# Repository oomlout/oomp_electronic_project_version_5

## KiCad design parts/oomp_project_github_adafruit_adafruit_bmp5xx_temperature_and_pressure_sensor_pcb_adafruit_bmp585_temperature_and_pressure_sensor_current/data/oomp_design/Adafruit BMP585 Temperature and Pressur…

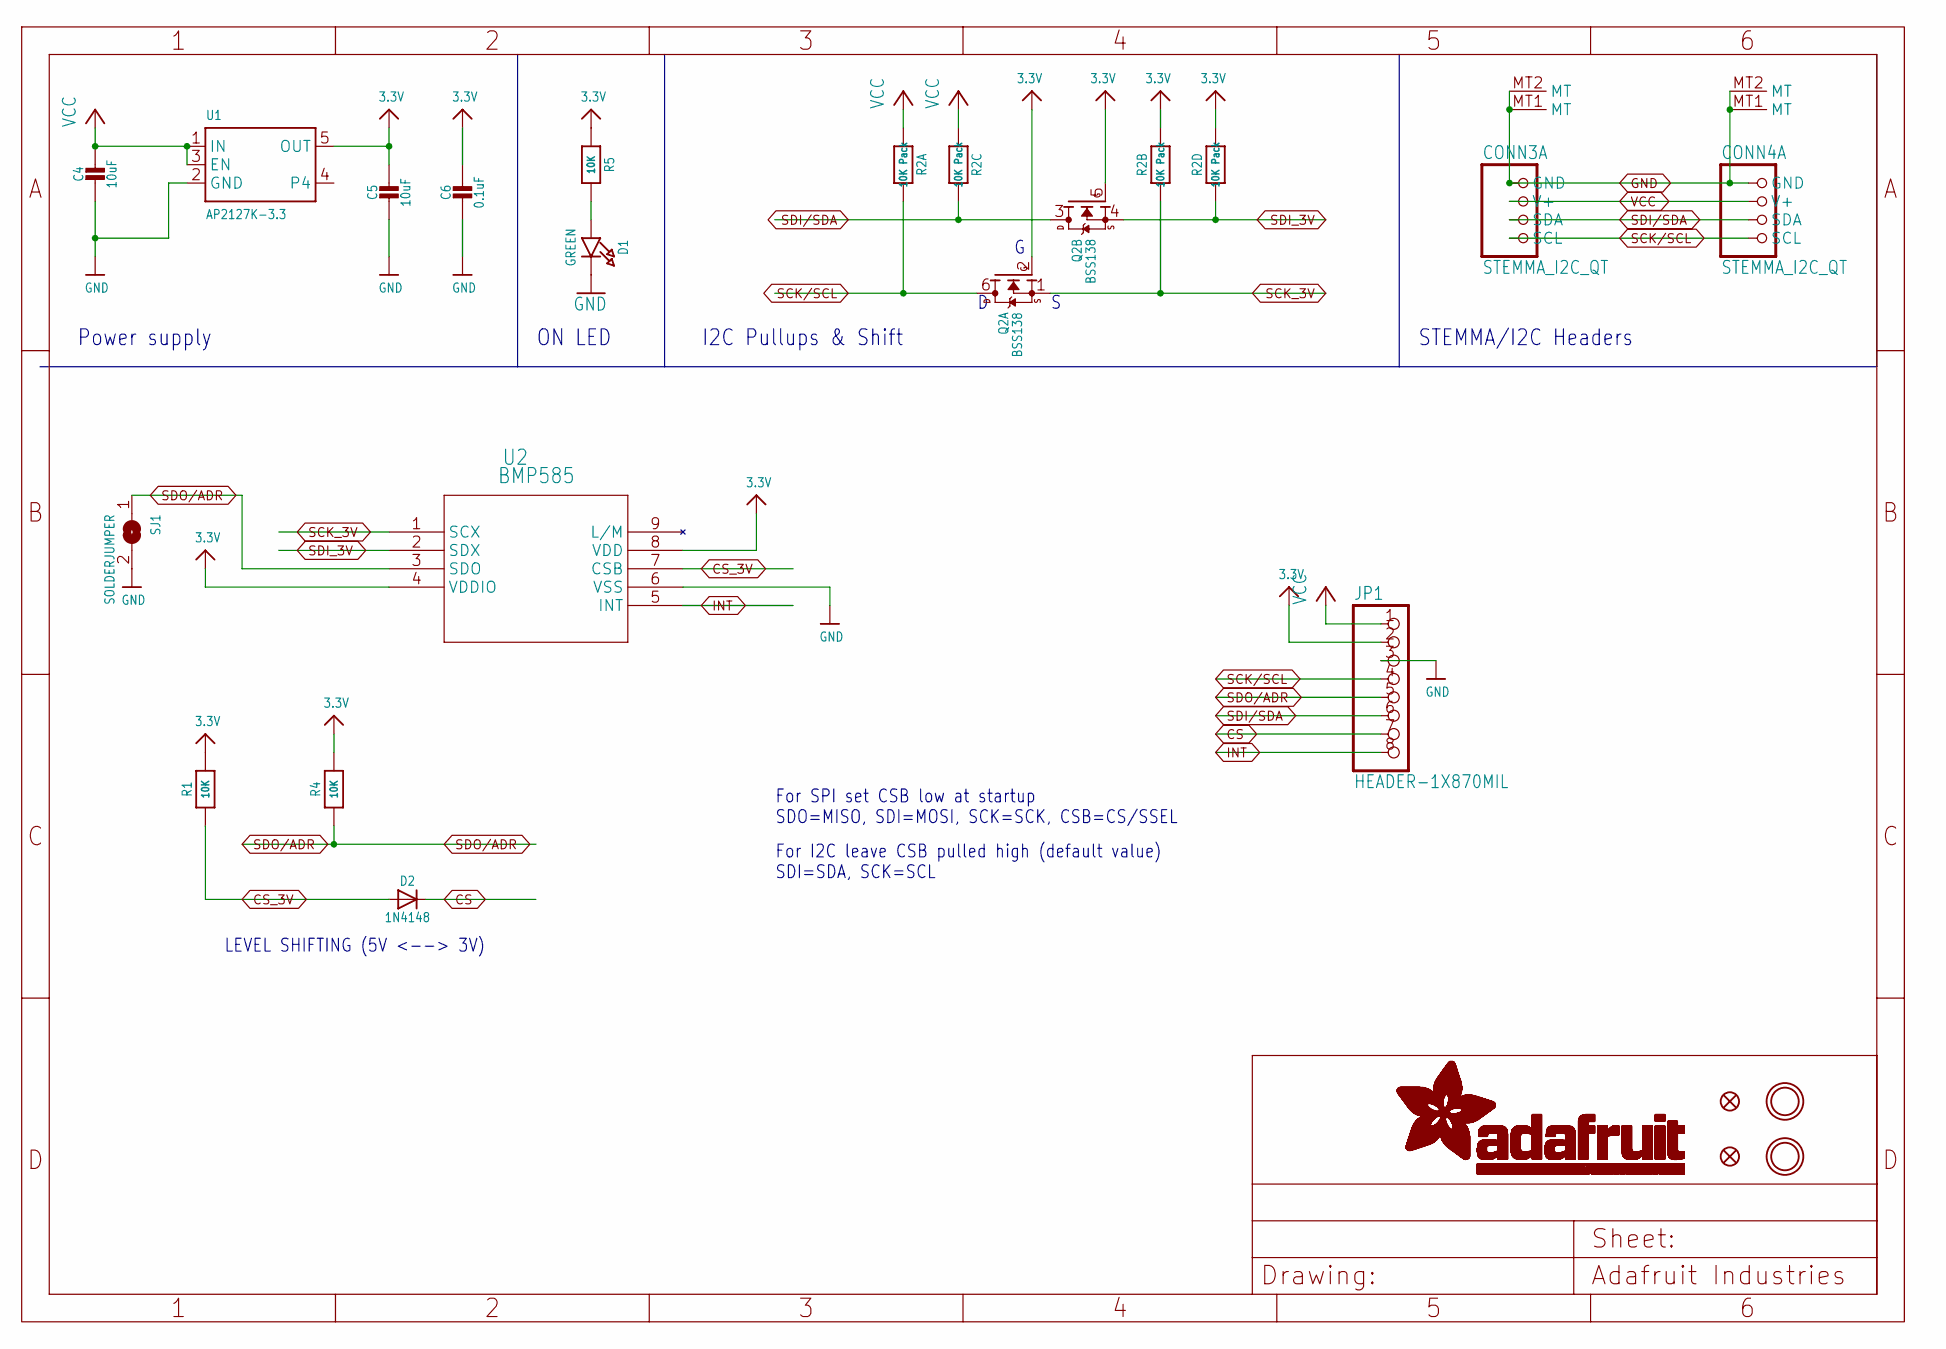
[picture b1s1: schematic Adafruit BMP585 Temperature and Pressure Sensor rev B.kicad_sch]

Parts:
C4, C5: 10uF; 0805-NO
C6: 0.1uF; 0603-NO
CONN3, CONN4: STEMMA_I2C_QT; JST_SH4; LCSC C2845363
D1: GREEN; CHIPLED_0603_NOOUTLINE
D2: 1N4148; SOD-323
FID3, FID4: FIDUCIAL_0.5MM
JP1: HEADER-1X870MIL; 1X08_ROUND_70
Q2: BSS138; SOT363; JLC_ROTATION 270
R1, R4, R5: 10K; 0603-NO
R2: 10K Pack; RESPACK_4X0603
SJ1: SOLDERJUMPER; SOLDERJUMPER_ARROW_NOPASTE
U1: AP2127K-3.3; SOT23-5; JLC_ROTATION 270
U2: BMP585; LGA9_BMP585_BOS; MANUFACTURER_PART_NUMBER BMP585
U$40, U$41: MOUNTINGHOLE2.5; MOUNTINGHOLE_2.5_PLATED

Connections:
3.3V: C5.1, C6.1, JP1.2, Q2.2 (G), Q2.5 (G), R1.2, R2.2 (1), R2.4 (1), R4.2, R5.1, U1.5 (OUT), U2.4 (VDDIO), U2.8 (VDD)
CS: D2.C, JP1.7
CS_3V: D2.A, R1.1, U2.7 (CSB)
GND: C4.2, C5.2, C6.2, CONN3.1 (GND), CONN3.MT1 (MT), CONN3.MT2 (MT), CONN4.1 (GND), CONN4.MT1 (MT), CONN4.MT2 (MT), D1.C, JP1.3, SJ1.2, U1.2 (GND), U2.6 (VSS)
INT: JP1.8, U2.5 (INT)
unnamed: D1.A, R5.2
SCK/SCL: CONN3.4 (SCL), CONN4.4 (SCL), JP1.4, Q2.6 (D), R2.8 (2)
SCK_3V: Q2.1 (S), R2.7 (2), U2.1 (SCX)
SDI/SDA: CONN3.3 (SDA), CONN4.3 (SDA), JP1.6, Q2.3 (D), R2.6 (2)
SDI_3V: Q2.4 (S), R2.5 (2), U2.2 (SDX)
SDO/ADR: JP1.5, R4.1, SJ1.1, U2.3 (SDO)
VCC: C4.1, CONN3.2 (V+), CONN4.2 (V+), JP1.1, R2.1, R2.3 (1), U1.1 (IN), U1.3 (EN)

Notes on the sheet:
ON LED
Power supply
I2C Pullups & Shift
LEVEL SHIFTING (5V <--> 3V)
For SPI set CSB low at startup SDO=MISO, SDI=MOSI, SCK=SCK, CSB=CS/SSEL
STEMMA/I2C Headers
For I2C leave CSB pulled high (default value) SDI=SDA, SCK=SCL

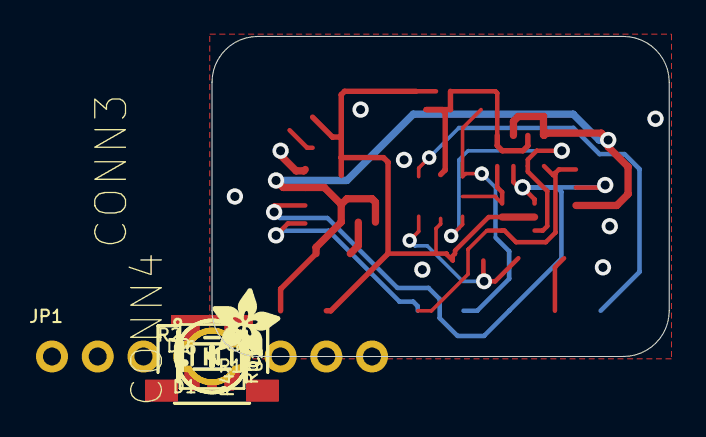
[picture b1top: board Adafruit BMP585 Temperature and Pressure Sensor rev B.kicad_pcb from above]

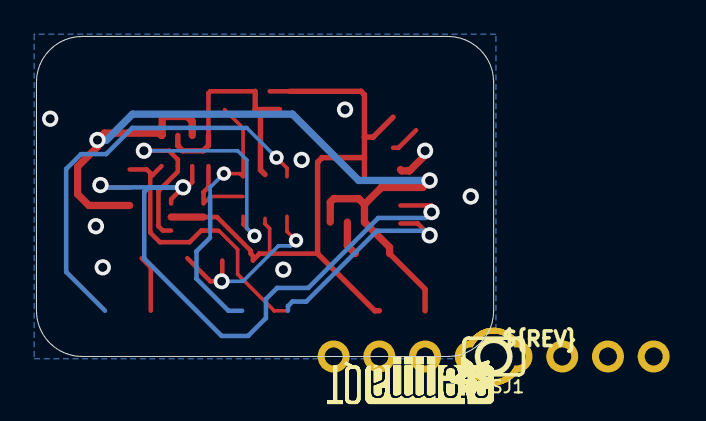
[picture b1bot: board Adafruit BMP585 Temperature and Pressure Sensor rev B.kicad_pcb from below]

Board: 2 copper layers, 25.4 x 17.8 mm, 40 parts (11 on the bottom side), 12 nets.

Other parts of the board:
PLABEL14: PLABEL14
PLABEL15: PLABEL15
PLABEL16: PLABEL16
PLABEL17: PLABEL17
PLABEL18: PLABEL18
PLABEL19: PLABEL19
PLABEL20: PLABEL20
PLABEL21: PLABEL21
PLABEL22: PLABEL22
PLABEL23: PLABEL23
PLABEL24: PLABEL24
PLABEL25: PLABEL25
PLABEL26: PLABEL26
PLABEL27: PLABEL27
U$6, U$7: ADAFRUIT_2.5MM
U$46: ADAFRUIT_3.5MM
U$47: PCBFEAT-REV-040
U$48, U$49: STEMMAQT

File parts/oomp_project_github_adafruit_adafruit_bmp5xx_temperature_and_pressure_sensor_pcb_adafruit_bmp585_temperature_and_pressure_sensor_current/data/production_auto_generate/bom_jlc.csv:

Comment,Designator,Footprint,LCSC Part #
,JP1,1X08_ROUND_70,C492421
,"U$6,U$7",ADAFRUIT_2.5MM,
,U$46,ADAFRUIT_3.5MM,
,U$47,PCBFEAT-REV-040,
,PLABEL14,PLABEL14,
,PLABEL15,PLABEL15,
,PLABEL16,PLABEL16,
,PLABEL17,PLABEL17,
,PLABEL18,PLABEL18,
,PLABEL19,PLABEL19,
,PLABEL20,PLABEL20,
,PLABEL21,PLABEL21,
,PLABEL22,PLABEL22,
,PLABEL23,PLABEL23,
,PLABEL24,PLABEL24,
,PLABEL25,PLABEL25,
,PLABEL26,PLABEL26,
,PLABEL27,PLABEL27,
,"U$48,U$49",STEMMAQT,
0.1uF,C6,0603-NO,C14663
10K,"R1,R4,R5",0603-NO,C98220
10K Pack,R2,RESPACK_4X0603,C98220
10uF,"C4,C5",0805-NO,
1N4148,D2,SOD-323,
AP2127K-3.3,U1,SOT23-5,
BMP585,U2,LGA9_BMP585_BOS,
BSS138,Q2,SOT363,
GREEN,D1,CHIPLED_0603_NOOUTLINE,
STEMMA_I2C_QT,"CONN3,CONN4",JST_SH4,C160404

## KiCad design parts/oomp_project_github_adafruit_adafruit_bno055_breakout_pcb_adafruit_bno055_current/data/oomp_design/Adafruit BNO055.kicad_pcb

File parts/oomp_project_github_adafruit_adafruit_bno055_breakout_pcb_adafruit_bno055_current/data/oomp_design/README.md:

# OOMP KiCad design copy

Open `Adafruit BNO055.kicad_pro` (or the `.kicad_pcb` / `.kicad_sch`) in KiCad. Local OOMP libraries are under `libraries/`. Original inputs are preserved in [../original/](../original/).

Only verified unchanged installed KiCad defaults were renamed. Modified, custom, unmatched and unavailable items remain unchanged. Soldering variants are never swapped during conversion. Existing pad coordinates, nets and UUIDs are preserved.

See [conversion_report.yaml](conversion_report.yaml) for every conversion and skip. Copy this directory before editing; regeneration refuses to overwrite edited design files.

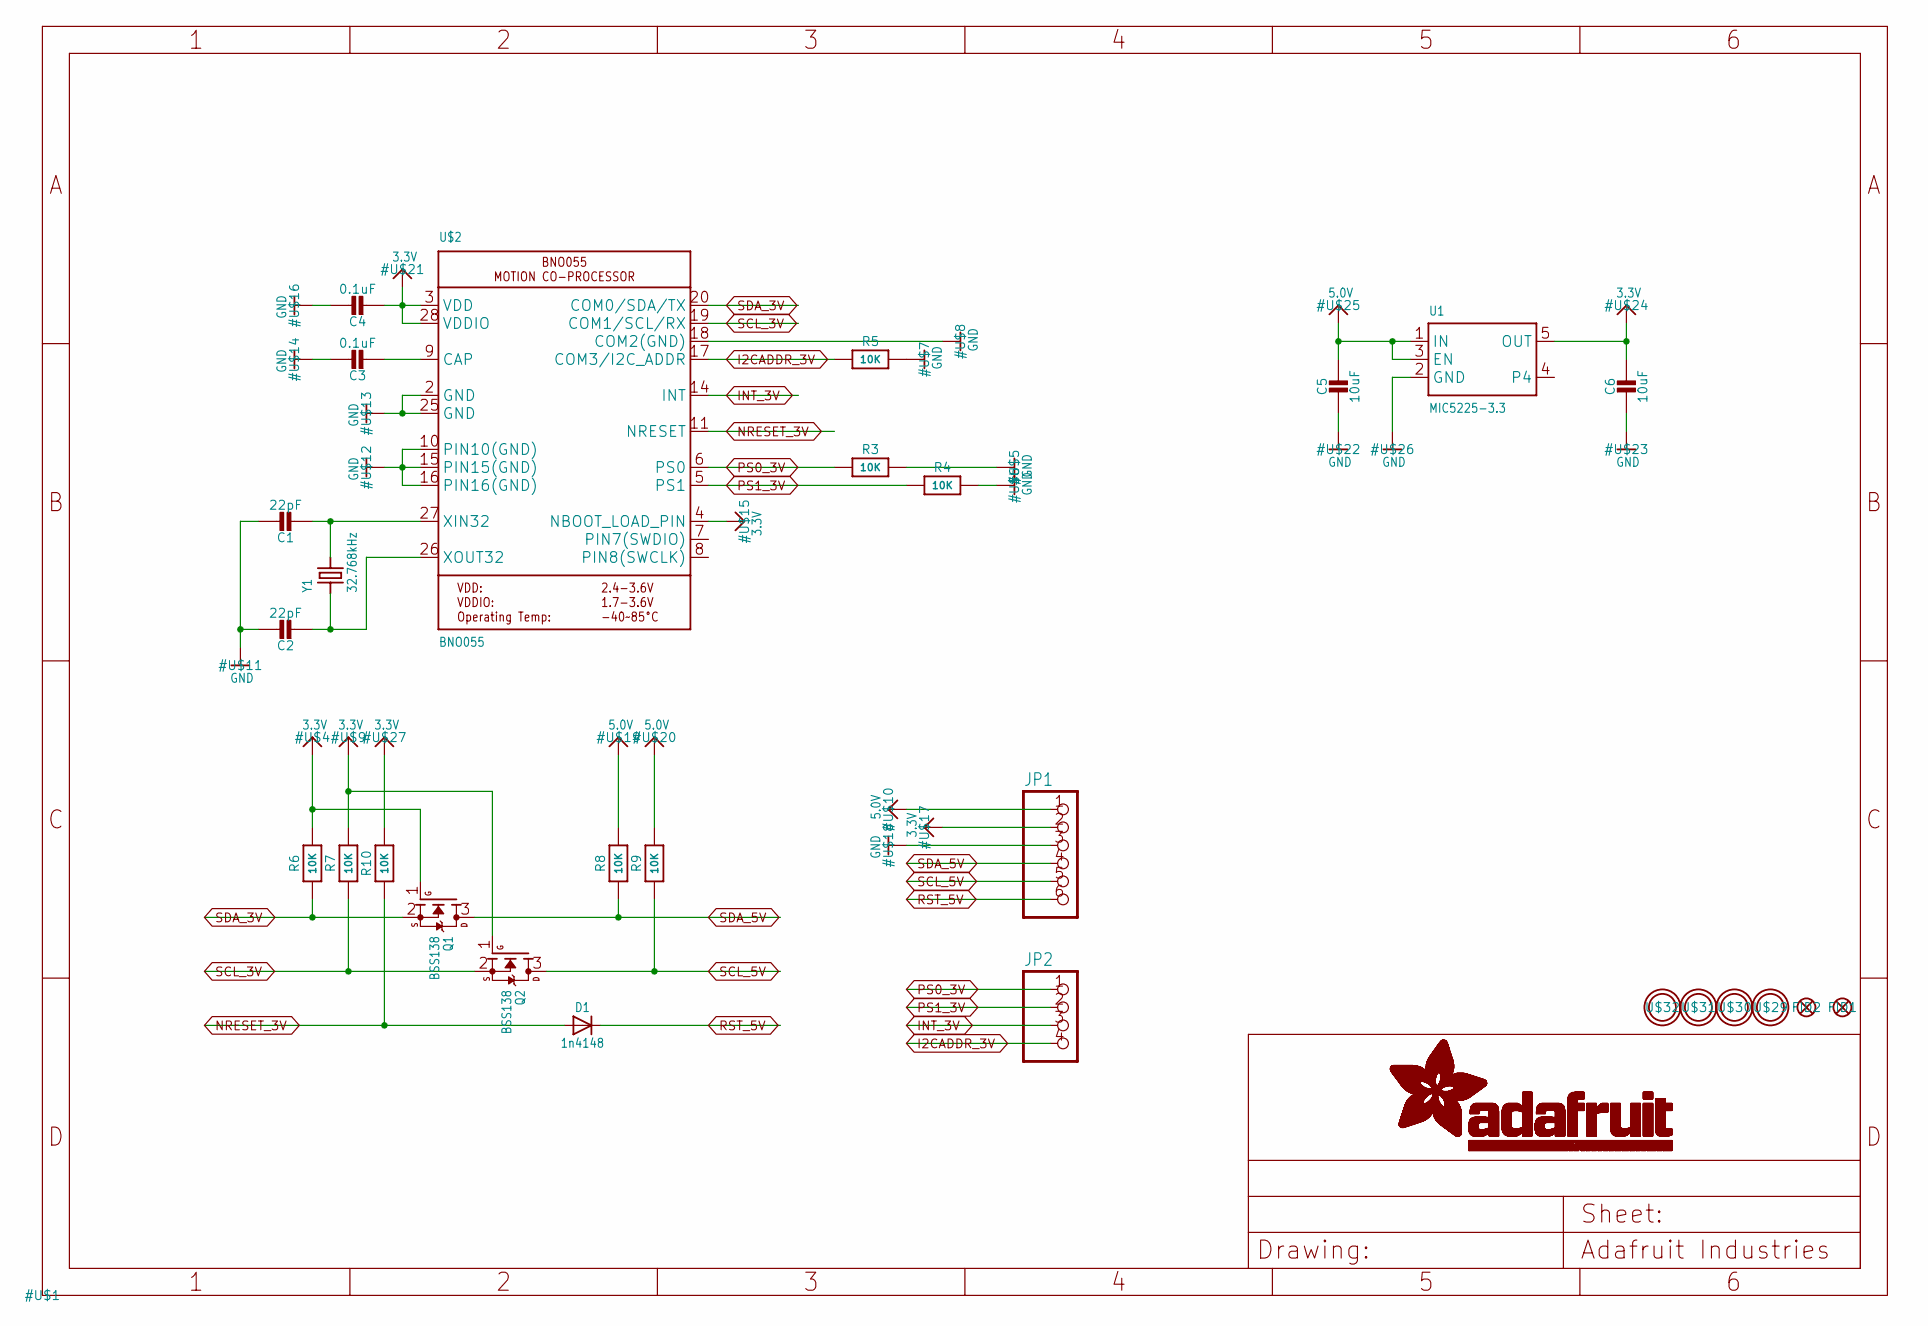
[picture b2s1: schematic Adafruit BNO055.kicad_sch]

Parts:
C1, C2: 22pF; 0805-NO
C3: 0.1uF; 0805-NO
C4: 0.1uF; 0805_10MGAP
C5: 10uF; 0805-NO
C6: 10uF; 0805_10MGAP
D1: 1n4148; SOD-323
FID1, FID2: FIDUCIAL""; FIDUCIAL_1MM
JP1: HEADER-1X676MIL; 1X06_ROUND_76
JP2: HEADER-1X476MIL; 1X04_ROUND_76
Q1, Q2: BSS138; SOT23-WIDE
R3, R4, R5, R6, R7, R10: 10K; 0805-NO
R8, R9: 10K; _0805MP
U1: MIC5225-3.3; SOT23-5
U$2: BNO055
U$29, U$30, U$31, U$32: MOUNTINGHOLE2.5_THICK; MOUNTINGHOLE_2.5_PLATED_THICK
Y1: 32.768kHz; CRYSTAL_8X3.8

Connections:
3.3V: C4.2, C6.1, JP1.2, Q1.1 (G), Q2.1 (G), R6.2, R7.2, R10.2, U1.5 (OUT), U$2.3 (VDD), U$2.4 (NBOOT_LOAD_PIN), U$2.28 (VDDIO)
5.0V: C5.1, JP1.1, R8.2, R9.2, U1.1 (IN), U1.3 (EN)
GND: C1.1, C2.1, C3.1, C4.1, C5.2, C6.2, JP1.3, R3.2, R4.2, R5.2, U1.2 (GND), U$2.2 (GND), U$2.10 (PIN10(GND)), U$2.15 (PIN15(GND)), U$2.16 (PIN16(GND)), U$2.18 (COM2(GND)), U$2.25 (GND)
I2CADDR_3V: JP2.4, R5.1, U$2.17 (COM3/I2C_ADDR)
INT_3V: JP2.3, U$2.14 (INT)
unnamed: C1.2, U$2.27 (XIN32), Y1.P$4 (2)
unnamed: C2.2, U$2.26 (XOUT32), Y1.P$1 (1)
unnamed: C3.2, U$2.9 (CAP)
NRESET_3V: D1.A, R10.1, U$2.11 (NRESET)
PS0_3V: JP2.1, R3.1, U$2.6 (PS0)
PS1_3V: JP2.2, R4.1, U$2.5 (PS1)
RST_5V: D1.C, JP1.6
SCL_3V: Q2.2 (S), R7.1, U$2.19 (COM1/SCL/RX)
SCL_5V: JP1.5, Q2.3 (D), R9.1
SDA_3V: Q1.2 (S), R6.1, U$2.20 (COM0/SDA/TX)
SDA_5V: JP1.4, Q1.3 (D), R8.1

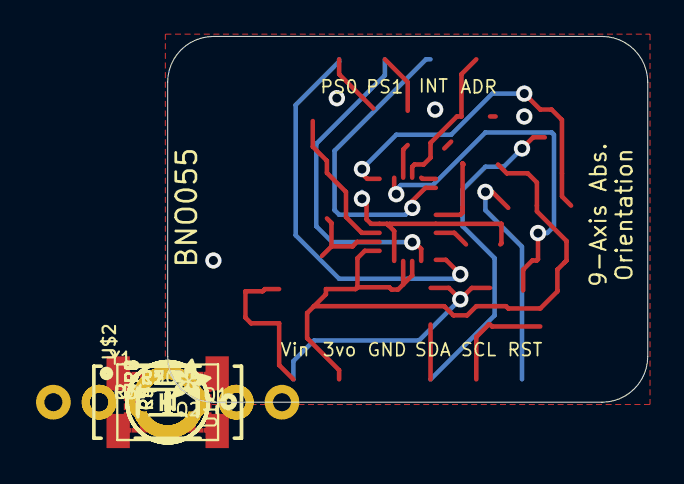
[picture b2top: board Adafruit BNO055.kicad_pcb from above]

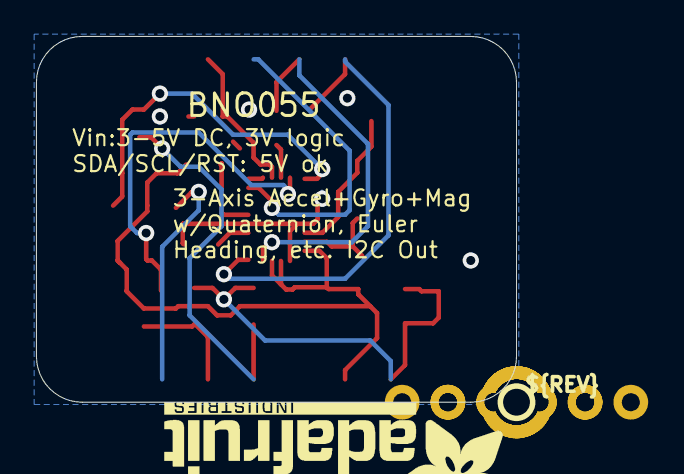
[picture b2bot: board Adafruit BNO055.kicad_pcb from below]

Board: 2 copper layers, 26.7 x 20.3 mm, 31 parts (2 on the bottom side), 16 nets.

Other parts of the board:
U$3: PCBFEAT-REV-040
U$28: ADAFRUIT_TEXT_20MM
U$33: ADAFRUIT_2.5MM

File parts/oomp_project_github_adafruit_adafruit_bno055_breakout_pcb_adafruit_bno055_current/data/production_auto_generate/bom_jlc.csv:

Comment,Designator,Footprint,LCSC Part #
,JP2,Adafruit BNO055-import-fps:1X04_ROUND_76,C42431795
,JP1,Adafruit BNO055-import-fps:1X06_ROUND_76,C37208
,U$33,Adafruit BNO055-import-fps:ADAFRUIT_2.5MM,
,U$28,Adafruit BNO055-import-fps:ADAFRUIT_TEXT_20MM,
,U$3,Adafruit BNO055-import-fps:PCBFEAT-REV-040,
0.1uF,C3,Adafruit BNO055-import-fps:0805-NO,
0.1uF,C4,Adafruit BNO055-import-fps:0805_10MGAP,
10K,"R3,R4,R5,R6,R7,R10",Adafruit BNO055-import-fps:0805-NO,C17414
10K,"R8,R9",Adafruit BNO055-import-fps:_0805MP,C17414
10uF,C5,Adafruit BNO055-import-fps:0805-NO,
10uF,C6,Adafruit BNO055-import-fps:0805_10MGAP,
1n4148,D1,Adafruit BNO055-import-fps:SOD-323,
22pF,"C1,C2",Adafruit BNO055-import-fps:0805-NO,
32.768kHz,Y1,Adafruit BNO055-import-fps:CRYSTAL_8X3.8,
BNO055,U$2,Adafruit BNO055-import-fps:BNO055,
BSS138,"Q1,Q2",Adafruit BNO055-import-fps:SOT23-WIDE,C52895
MIC5225-3.3,U1,Adafruit BNO055-import-fps:SOT23-5,

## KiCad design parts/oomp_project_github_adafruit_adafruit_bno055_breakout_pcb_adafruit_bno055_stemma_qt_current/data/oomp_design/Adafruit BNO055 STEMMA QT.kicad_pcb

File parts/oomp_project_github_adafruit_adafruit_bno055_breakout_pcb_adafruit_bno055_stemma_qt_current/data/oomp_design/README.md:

# OOMP KiCad design copy

Open `Adafruit BNO055 STEMMA QT.kicad_pro` (or the `.kicad_pcb` / `.kicad_sch`) in KiCad. Local OOMP libraries are under `libraries/`. Original inputs are preserved in [../original/](../original/).

Only verified unchanged installed KiCad defaults were renamed. Modified, custom, unmatched and unavailable items remain unchanged. Soldering variants are never swapped during conversion. Existing pad coordinates, nets and UUIDs are preserved.

See [conversion_report.yaml](conversion_report.yaml) for every conversion and skip. Copy this directory before editing; regeneration refuses to overwrite edited design files.

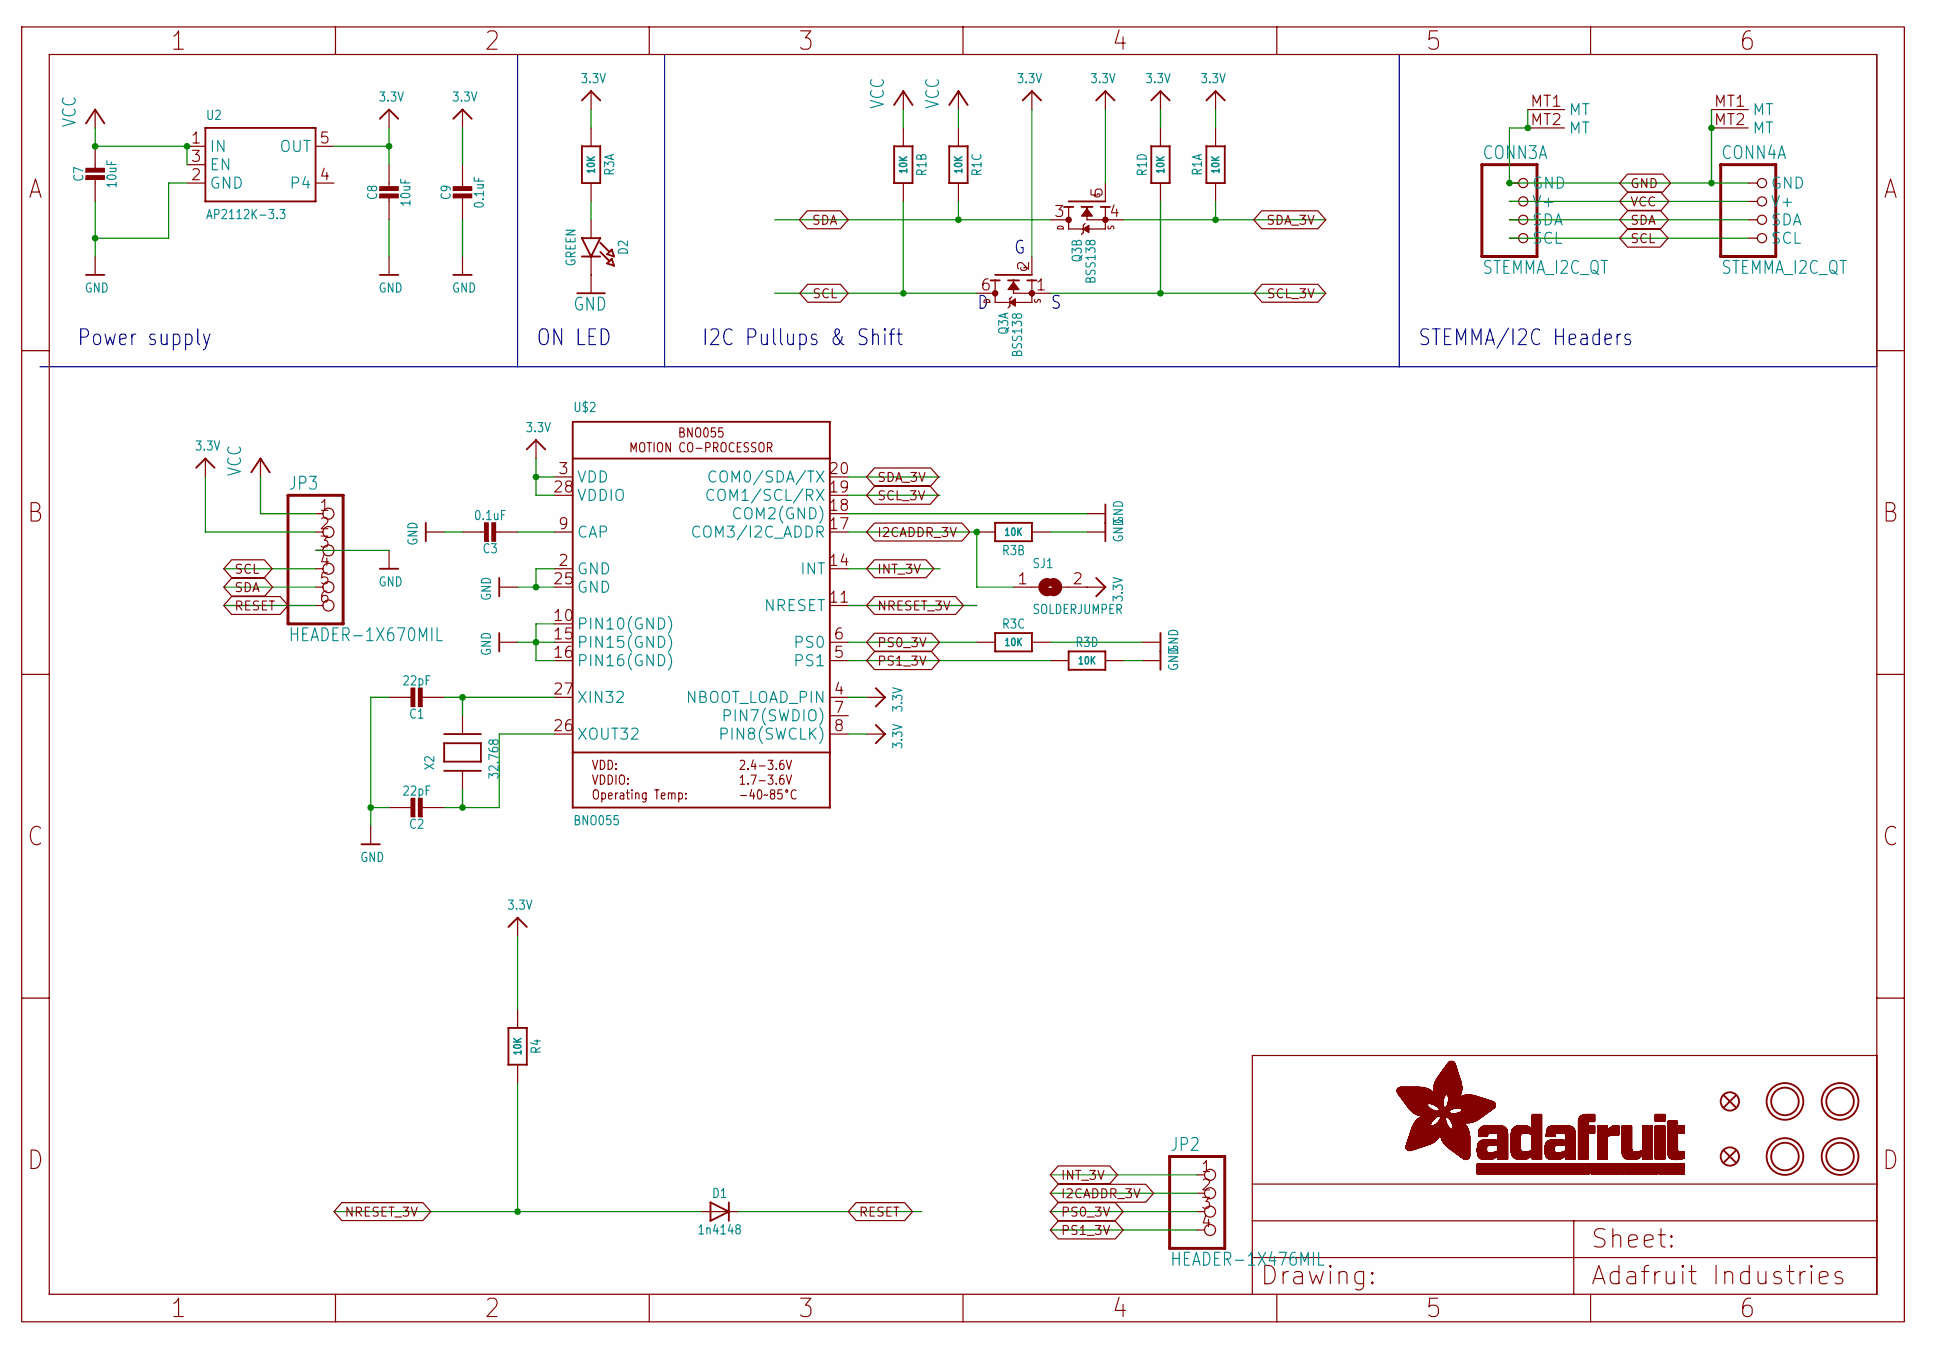
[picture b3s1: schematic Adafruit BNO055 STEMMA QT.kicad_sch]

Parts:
C1, C2: 22pF; 0603-NO
C3, C9: 0.1uF; 0603-NO
C7, C8: 10uF; 0805-NO
CONN3, CONN4: STEMMA_I2C_QT; JST_SH4
D1: 1n4148; SOD-323
D2: GREEN; CHIPLED_0603_NOOUTLINE
FID3, FID4: FIDUCIAL_1MM
JP2: HEADER-1X476MIL; 1X04_ROUND_76
JP3: HEADER-1X670MIL; 1X06_ROUND_70
Q3: BSS138; SOT363
R1, R3: 10K; RESPACK_4X0603
R4: 10K; 0603-NO
SJ1: SOLDERJUMPER; SOLDERJUMPER_ARROW_NOPASTE
U2: AP2112K-3.3; SOT23-5
U$2: BNO055
U$45, U$46, U$48, U$49: MOUNTINGHOLE2.5; MOUNTINGHOLE_2.5_PLATED
X2: 32.768; XTAL3215

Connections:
3.3V: C8.1, C9.1, JP3.2, Q3.2 (G), Q3.5 (G), R1.1, R1.4 (1), R3.1, R4.1, SJ1.2, U2.5 (OUT), U$2.3 (VDD), U$2.4 (NBOOT_LOAD_PIN), U$2.8 (PIN8(SWCLK)), U$2.28 (VDDIO)
GND: C1.1, C2.1, C3.1, C7.2, C8.2, C9.2, CONN3.1 (GND), CONN3.MT1 (MT), CONN3.MT2 (MT), CONN4.1 (GND), CONN4.MT1 (MT), CONN4.MT2 (MT), D2.C, JP3.3, R3.2 (1), R3.5 (2), R3.6 (2), U2.2 (GND), U$2.2 (GND), U$2.10 (PIN10(GND)), U$2.15 (PIN15(GND)), U$2.16 (PIN16(GND)), U$2.18 (COM2(GND)), U$2.25 (GND)
I2CADDR_3V: JP2.2, R3.7 (2), SJ1.1, U$2.17 (COM3/I2C_ADDR)
INT_3V: JP2.1, U$2.14 (INT)
unnamed: C1.2, U$2.27 (XIN32), X2.P$2
unnamed: C2.2, U$2.26 (XOUT32), X2.P$1
unnamed: C3.2, U$2.9 (CAP)
unnamed: D2.A, R3.8 (2)
NRESET_3V: D1.A, R4.2, U$2.11 (NRESET)
PS0_3V: JP2.3, R3.3 (1), U$2.6 (PS0)
PS1_3V: JP2.4, R3.4 (1), U$2.5 (PS1)
RESET: D1.C, JP3.6
SCL: CONN3.4 (SCL), CONN4.4 (SCL), JP3.4, Q3.6 (D), R1.7 (2)
SCL_3V: Q3.1 (S), R1.5 (2), U$2.19 (COM1/SCL/RX)
SDA: CONN3.3 (SDA), CONN4.3 (SDA), JP3.5, Q3.3 (D), R1.6 (2)
SDA_3V: Q3.4 (S), R1.8 (2), U$2.20 (COM0/SDA/TX)
VCC: C7.1, CONN3.2 (V+), CONN4.2 (V+), JP3.1, R1.2 (1), R1.3 (1), U2.1 (IN), U2.3 (EN)

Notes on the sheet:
Power supply
I2C Pullups & Shift
STEMMA/I2C Headers
ON LED

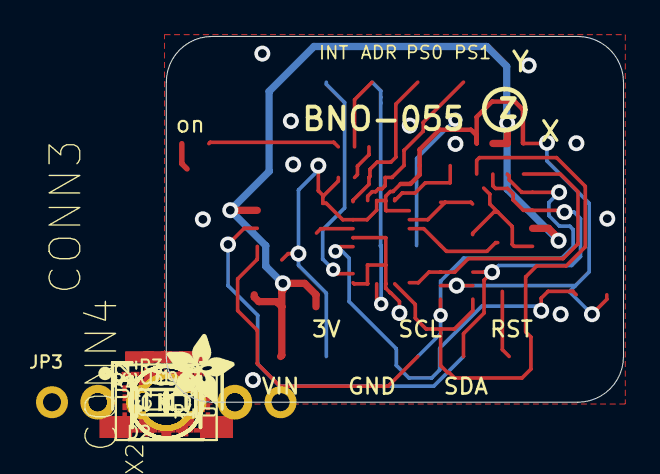
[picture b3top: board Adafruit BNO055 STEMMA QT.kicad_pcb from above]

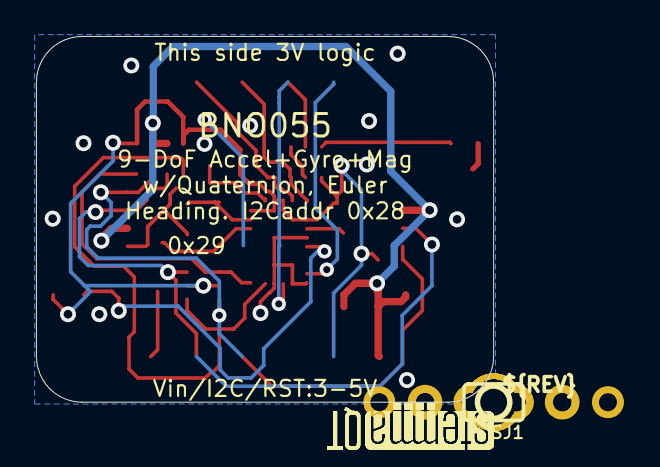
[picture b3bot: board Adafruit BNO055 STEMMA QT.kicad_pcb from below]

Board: 2 copper layers, 25.4 x 20.3 mm, 30 parts (4 on the bottom side), 17 nets.

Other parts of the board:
U$51: ADAFRUIT_3.5MM
U$52: PCBFEAT-REV-040
U$53, U$54: STEMMAQT

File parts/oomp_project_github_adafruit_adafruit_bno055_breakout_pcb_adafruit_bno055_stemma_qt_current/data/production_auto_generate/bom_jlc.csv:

Comment,Designator,Footprint,LCSC Part #
,JP2,Adafruit BNO055 STEMMA QT-import-fps:1X04_ROUND_76,C42431795
,JP3,Adafruit BNO055 STEMMA QT-import-fps:1X06_ROUND_70,C37208
,U$51,Adafruit BNO055 STEMMA QT-import-fps:ADAFRUIT_3.5MM,
,U$52,Adafruit BNO055 STEMMA QT-import-fps:PCBFEAT-REV-040,
,"U$53,U$54",Adafruit BNO055 STEMMA QT-import-fps:STEMMAQT,
0.1uF,"C3,C9",Adafruit BNO055 STEMMA QT-import-fps:0603-NO,C14663
10K,R4,Adafruit BNO055 STEMMA QT-import-fps:0603-NO,C98220
10K,"R1,R3",Adafruit BNO055 STEMMA QT-import-fps:RESPACK_4X0603,C98220
10uF,"C7,C8",Adafruit BNO055 STEMMA QT-import-fps:0805-NO,
1n4148,D1,Adafruit BNO055 STEMMA QT-import-fps:SOD-323,
22pF,"C1,C2",Adafruit BNO055 STEMMA QT-import-fps:0603-NO,C105620
32.768,X2,Adafruit BNO055 STEMMA QT-import-fps:XTAL3215,
AP2112K-3.3,U2,Adafruit BNO055 STEMMA QT-import-fps:SOT23-5,
BNO055,U$2,Adafruit BNO055 STEMMA QT-import-fps:BNO055,
BSS138,Q3,Adafruit BNO055 STEMMA QT-import-fps:SOT363,
GREEN,D2,Adafruit BNO055 STEMMA QT-import-fps:CHIPLED_0603_NOOUTLINE,
STEMMA_I2C_QT,"CONN3,CONN4",Adafruit BNO055 STEMMA QT-import-fps:JST_SH4,C160404

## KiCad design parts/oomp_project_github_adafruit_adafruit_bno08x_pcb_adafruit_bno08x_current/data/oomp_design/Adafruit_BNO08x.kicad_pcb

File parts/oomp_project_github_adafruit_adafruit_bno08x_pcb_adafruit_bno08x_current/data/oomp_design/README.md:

# OOMP KiCad design copy

Open `Adafruit_BNO08x.kicad_pro` (or the `.kicad_pcb` / `.kicad_sch`) in KiCad. Local OOMP libraries are under `libraries/`. Original inputs are preserved in [../original/](../original/).

Only verified unchanged installed KiCad defaults were renamed. Modified, custom, unmatched and unavailable items remain unchanged. Soldering variants are never swapped during conversion. Existing pad coordinates, nets and UUIDs are preserved.

See [conversion_report.yaml](conversion_report.yaml) for every conversion and skip. Copy this directory before editing; regeneration refuses to overwrite edited design files.

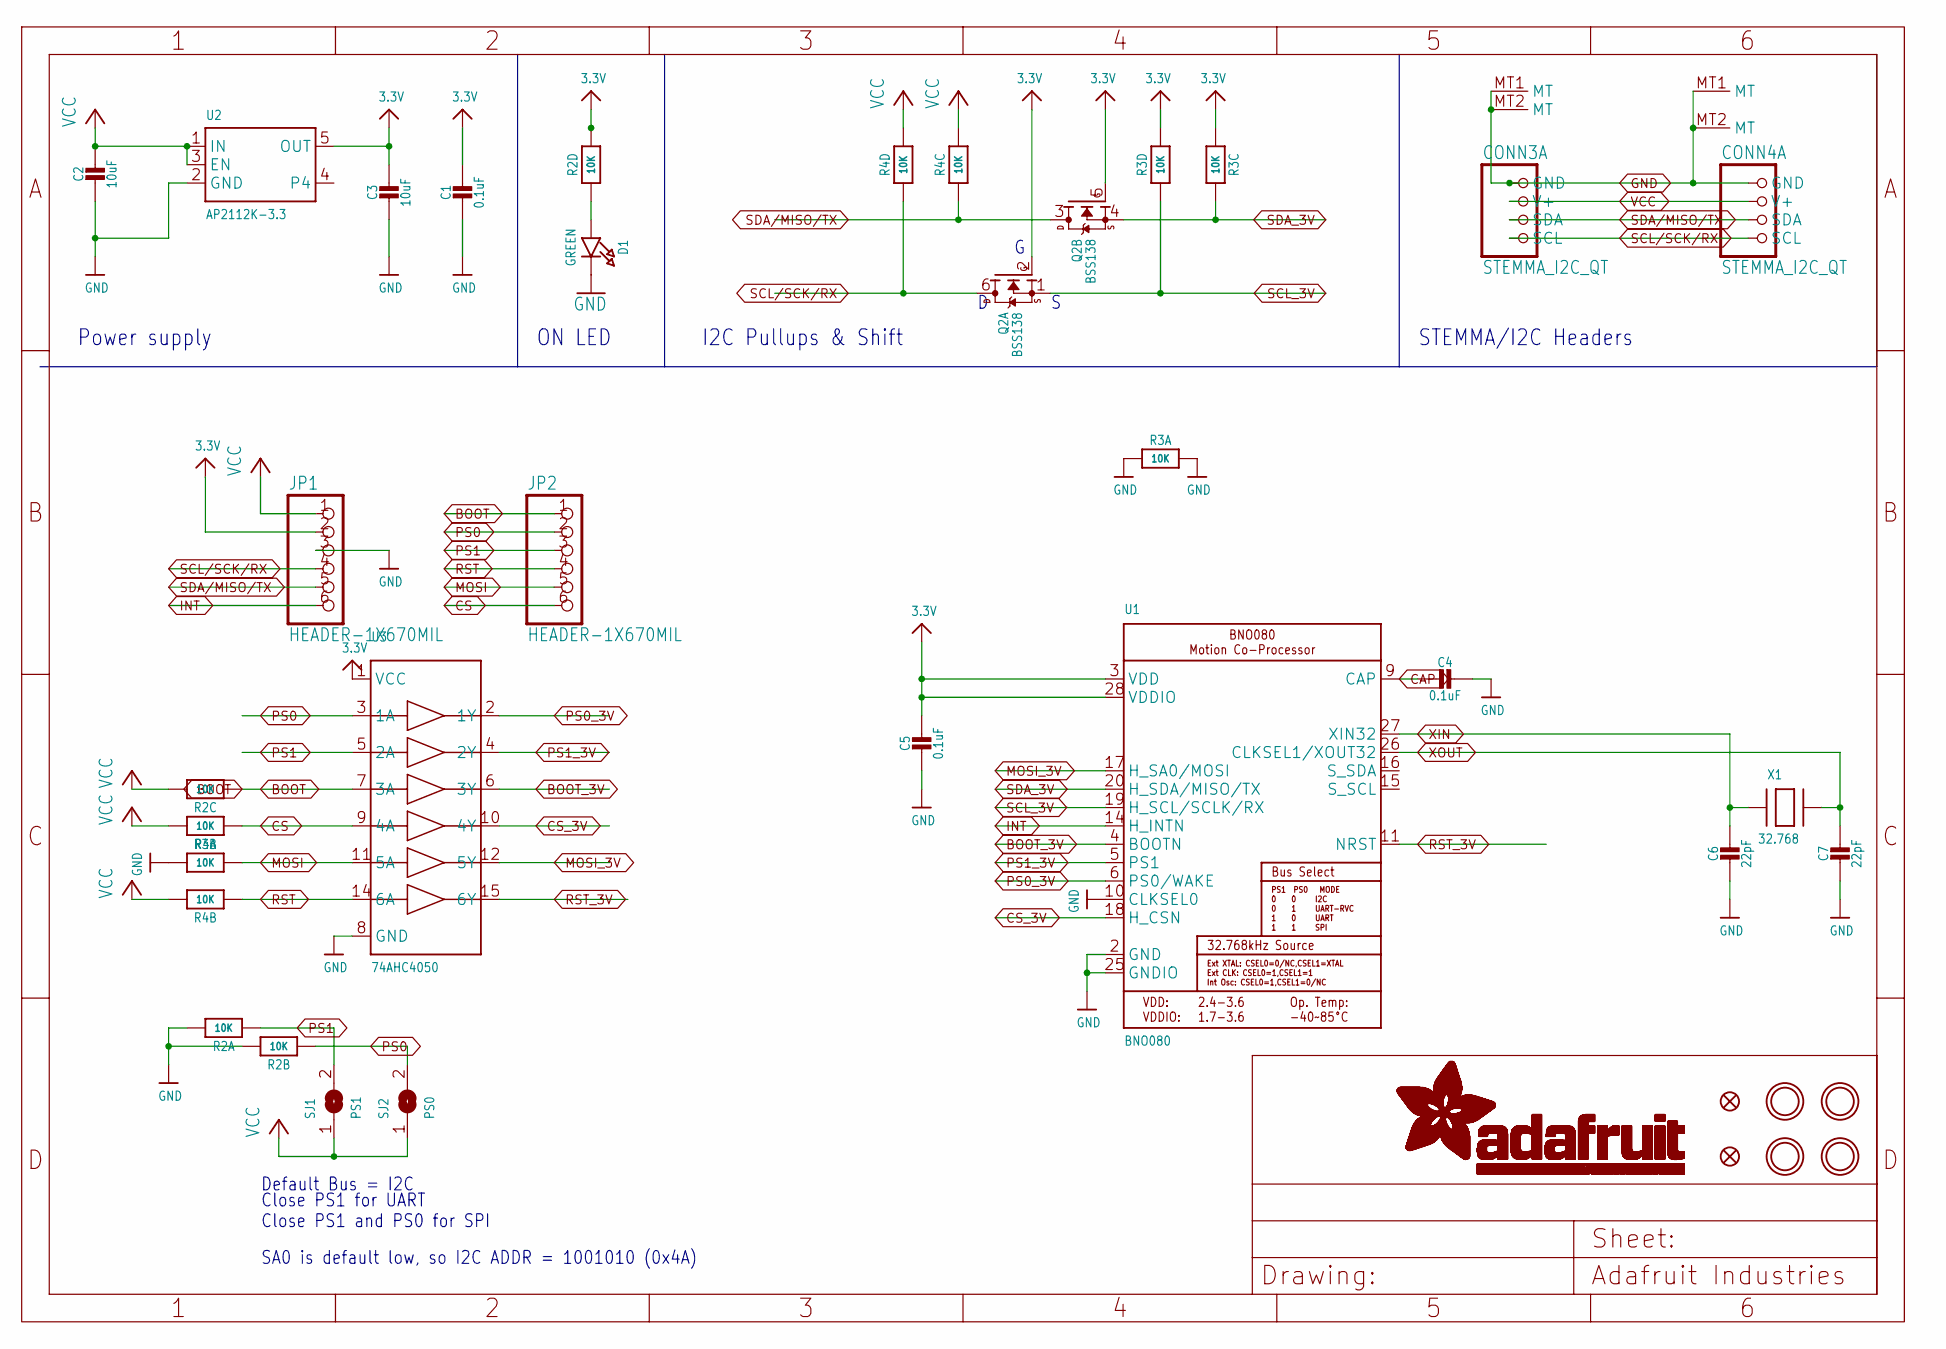
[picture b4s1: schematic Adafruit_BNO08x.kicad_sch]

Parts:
C1, C4, C5: 0.1uF; 0603-NO
C2, C3: 10uF; 0805-NO
C6, C7: 22pF; 0603-NO
CONN3, CONN4: STEMMA_I2C_QT; JST_SH4
D1: GREEN; CHIPLED_0603_NOOUTLINE
FID3, FID4: FIDUCIAL_1MM
JP1, JP2: HEADER-1X670MIL; 1X06_ROUND_70
Q2: BSS138; SOT363
R2, R3, R4: 10K; RESPACK_4X0603
SJ1: PS1; SOLDERJUMPER_ARROW_NOPASTE
SJ2: PS0; SOLDERJUMPER_ARROW_NOPASTE
U1: BNO080
U2: AP2112K-3.3; SOT23-5
U3: 74AHC4050; TSSOP16
U$1, U$17, U$19, U$21: MOUNTINGHOLE2.5; MOUNTINGHOLE_2.5_PLATED
X1: 32.768; XTAL3215

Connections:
3.3V: C1.1, C3.1, C5.1, JP1.2, Q2.2 (G), Q2.5 (G), R2.5 (2), R3.3 (1), R3.5 (2), U1.3 (VDD), U1.28 (VDDIO), U2.5 (OUT), U3.1 (VCC)
BOOT: JP2.1, R2.3 (1), U3.7 (3A)
BOOT_3V: U1.4 (BOOTN), U3.6 (3Y)
CAP: C4.2, U1.9 (CAP)
CS: JP2.6, R4.1, U3.9 (4A)
CS_3V: U1.18 (H_CSN), U3.10 (4Y)
GND: C1.2, C2.2, C3.2, C4.1, C5.2, C6.2, C7.2, CONN3.1 (GND), CONN3.MT1 (MT), CONN3.MT2 (MT), CONN4.1 (GND), CONN4.MT1 (MT), CONN4.MT2 (MT), D1.C, JP1.3, R2.7 (2), R2.8 (2), R3.1, R3.2 (1), R3.8 (2), U1.2 (GND), U1.10 (CLKSEL0), U1.25 (GNDIO), U2.2 (GND), U3.8 (GND)
INT: JP1.6, U1.14 (H_INTN)
MOSI: JP2.5, R3.7 (2), U3.11 (5A)
MOSI_3V: U1.17 (H_SA0/MOSI), U3.12 (5Y)
unnamed: D1.A, R2.4 (1)
PS0: JP2.2, R2.2 (1), SJ2.2, U3.3 (1A)
PS0_3V: U1.6 (PS0/WAKE), U3.2 (1Y)
PS1: JP2.3, R2.1, SJ1.2, U3.5 (2A)
PS1_3V: U1.5 (PS1), U3.4 (2Y)
RST: JP2.4, R4.2 (1), U3.14 (6A)
RST_3V: U1.11 (NRST), U3.15 (6Y)
SCL/SCK/RX: CONN3.4 (SCL), CONN4.4 (SCL), JP1.4, Q2.6 (D), R4.4 (1)
SCL_3V: Q2.1 (S), R3.4 (1), U1.19 (H_SCL/SCLK/RX)
SDA/MISO/TX: CONN3.3 (SDA), CONN4.3 (SDA), JP1.5, Q2.3 (D), R4.3 (1)
SDA_3V: Q2.4 (S), R3.6 (2), U1.20 (H_SDA/MISO/TX)
VCC: C2.1, CONN3.2 (V+), CONN4.2 (V+), JP1.1, R2.6 (2), R4.5 (2), R4.6 (2), R4.7 (2), R4.8 (2), SJ1.1, SJ2.1, U2.1 (IN), U2.3 (EN)
XIN: C6.1, U1.27 (XIN32), X1.P$1
XOUT: C7.1, U1.26 (CLKSEL1/XOUT32), X1.P$2

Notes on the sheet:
Close PS1 for UART Close PS1 and PS0 for SPI
SA0 is default low, so I2C ADDR = 1001010 (0x4A)
ON LED
Power supply
Default Bus = I2C
STEMMA/I2C Headers
I2C Pullups & Shift

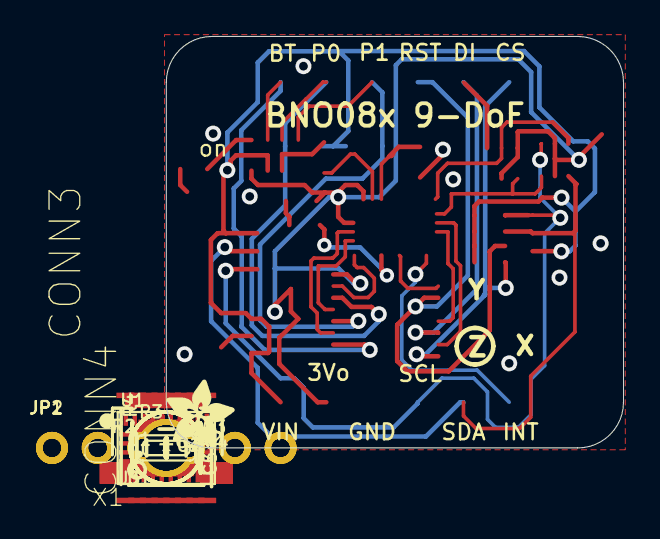
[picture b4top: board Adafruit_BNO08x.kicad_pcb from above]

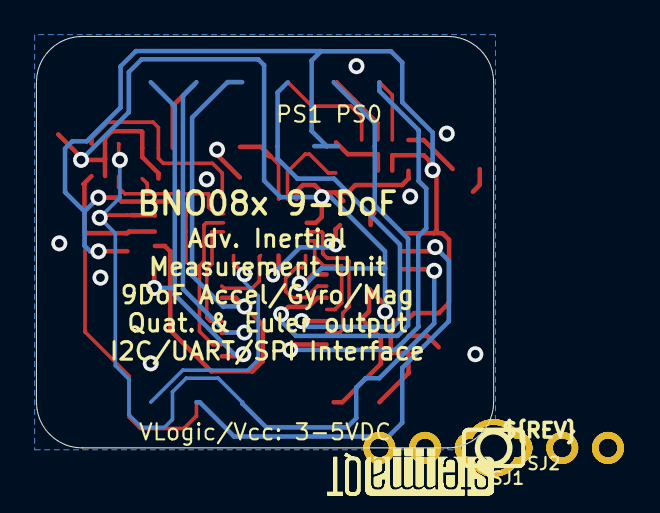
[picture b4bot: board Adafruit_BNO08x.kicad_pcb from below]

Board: 2 copper layers, 25.4 x 22.9 mm, 32 parts (5 on the bottom side), 24 nets.

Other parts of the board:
U$22: ADAFRUIT_3.5MM
U$25: PCBFEAT-REV-040
U$30, U$31: STEMMAQT

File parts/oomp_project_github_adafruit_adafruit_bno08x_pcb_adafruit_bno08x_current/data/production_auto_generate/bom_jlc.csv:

Comment,Designator,Footprint,LCSC Part #
,"JP1,JP2",Adafruit_BNO08x-import-fps:1X06_ROUND_70,C37208
,U$22,Adafruit_BNO08x-import-fps:ADAFRUIT_3.5MM,
,U$25,Adafruit_BNO08x-import-fps:PCBFEAT-REV-040,
,"U$30,U$31",Adafruit_BNO08x-import-fps:STEMMAQT,
0.1uF,"C1,C4,C5",Adafruit_BNO08x-import-fps:0603-NO,C14663
10K,"R2,R3,R4",Adafruit_BNO08x-import-fps:RESPACK_4X0603,C98220
10uF,"C2,C3",Adafruit_BNO08x-import-fps:0805-NO,
22pF,"C6,C7",Adafruit_BNO08x-import-fps:0603-NO,C105620
32.768,X1,Adafruit_BNO08x-import-fps:XTAL3215,
74AHC4050,U3,Adafruit_BNO08x-import-fps:TSSOP16,
AP2112K-3.3,U2,Adafruit_BNO08x-import-fps:SOT23-5,
BNO080,U1,Adafruit_BNO08x-import-fps:BNO080,
BSS138,Q2,Adafruit_BNO08x-import-fps:SOT363,
GREEN,D1,Adafruit_BNO08x-import-fps:CHIPLED_0603_NOOUTLINE,
STEMMA_I2C_QT,"CONN3,CONN4",Adafruit_BNO08x-import-fps:JST_SH4,C160404

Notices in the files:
parts and their libraries:
COPYRIGHT: Copyright (C) 2025 Ultra Librarian. All rights reserved.
